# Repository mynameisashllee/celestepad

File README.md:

# celestepad
so... i play the game celeste a little bit, and thought it'd be cool to have a macropad with the bindings i use! (the defaults... haha)

check out the demo on [reddit!](https://www.reddit.com/r/celestegame/comments/1mbj6k7/i_made_a_mini_keypad_to_play_celeste/)

## features
- celestepad uses 7 keys (climb [z], dash [x], jump [c] and arrow keys. yes, they look inconveniently placed but they work pretty fine)
- regular ol case (enhanced with air dry clay and craft skills)

here's how it looks with just the circuit board and 3d print:

here's how the case looks alone:

## pcb
schematic:<br>

pcb (some strawberries because.. celeste): <br>

## bom
- 7x cherry MX switches
- 7x DSA keycaps
- 4x M3x5mx4mm heatset inserts
- 4x M3x16mm screws
- 1x XIAO RP2040
- 1x case (with 2 printed parts)
- some air dry clay, paint, hot glue and felt

## extras
this is my first time doing hardware! making a pcb! 3d modelling! had to google a lot but it was worth it (:
if i have time later on, i'll try and make a cute strawberry case that can open up to show the macropad. maybe with hinges? we'll see!

update: i ended up using air dry clay for fun and i'm really happy with the crafty look it's got!

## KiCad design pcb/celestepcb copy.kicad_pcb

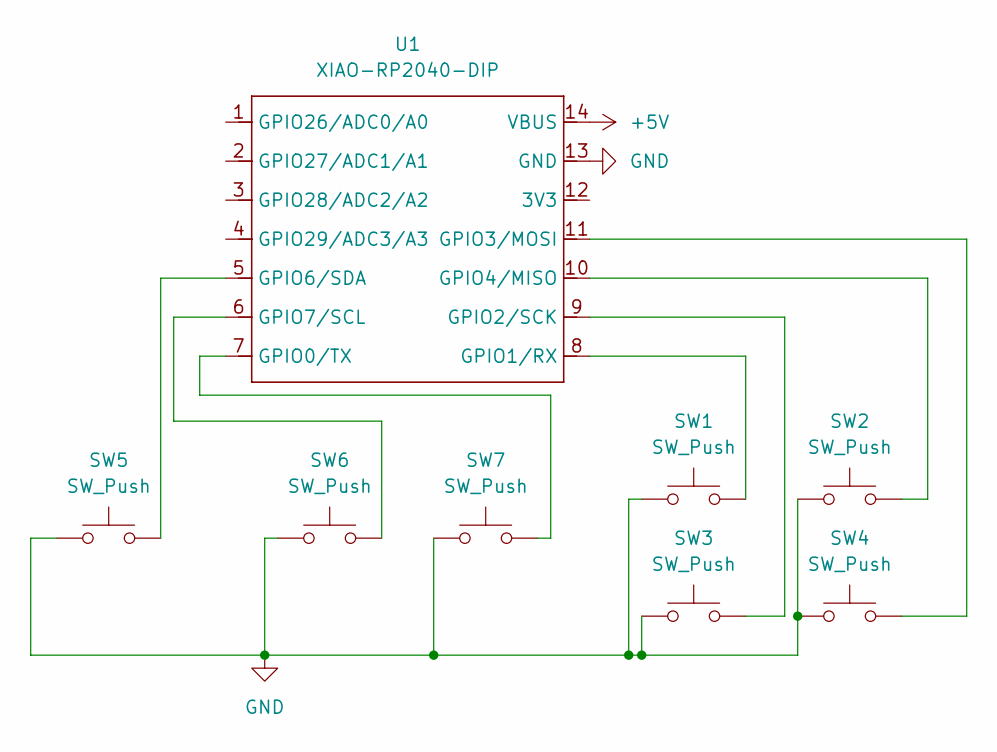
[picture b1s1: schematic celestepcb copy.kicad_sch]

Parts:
SW1, SW2, SW3, SW4, SW5, SW6, SW7: SW_Push; SW_Cherry_MX_1.00u_PCB
U1: XIAO-RP2040-DIP

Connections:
+5V: U1.14 (VBUS)
GND: SW1.1, SW2.1, SW3.1, SW4.1, SW5.1, SW6.1, SW7.1, U1.13 (GND)
unnamed: SW7.2, U1.7 (GPIO0/TX)
unnamed: SW1.2, U1.8 (GPIO1/RX)
unnamed: SW3.2, U1.9 (GPIO2/SCK)
unnamed: SW4.2, U1.11 (GPIO3/MOSI)
unnamed: SW2.2, U1.10 (GPIO4/MISO)
unnamed: SW5.2, U1.5 (GPIO6/SDA)
unnamed: SW6.2, U1.6 (GPIO7/SCL)

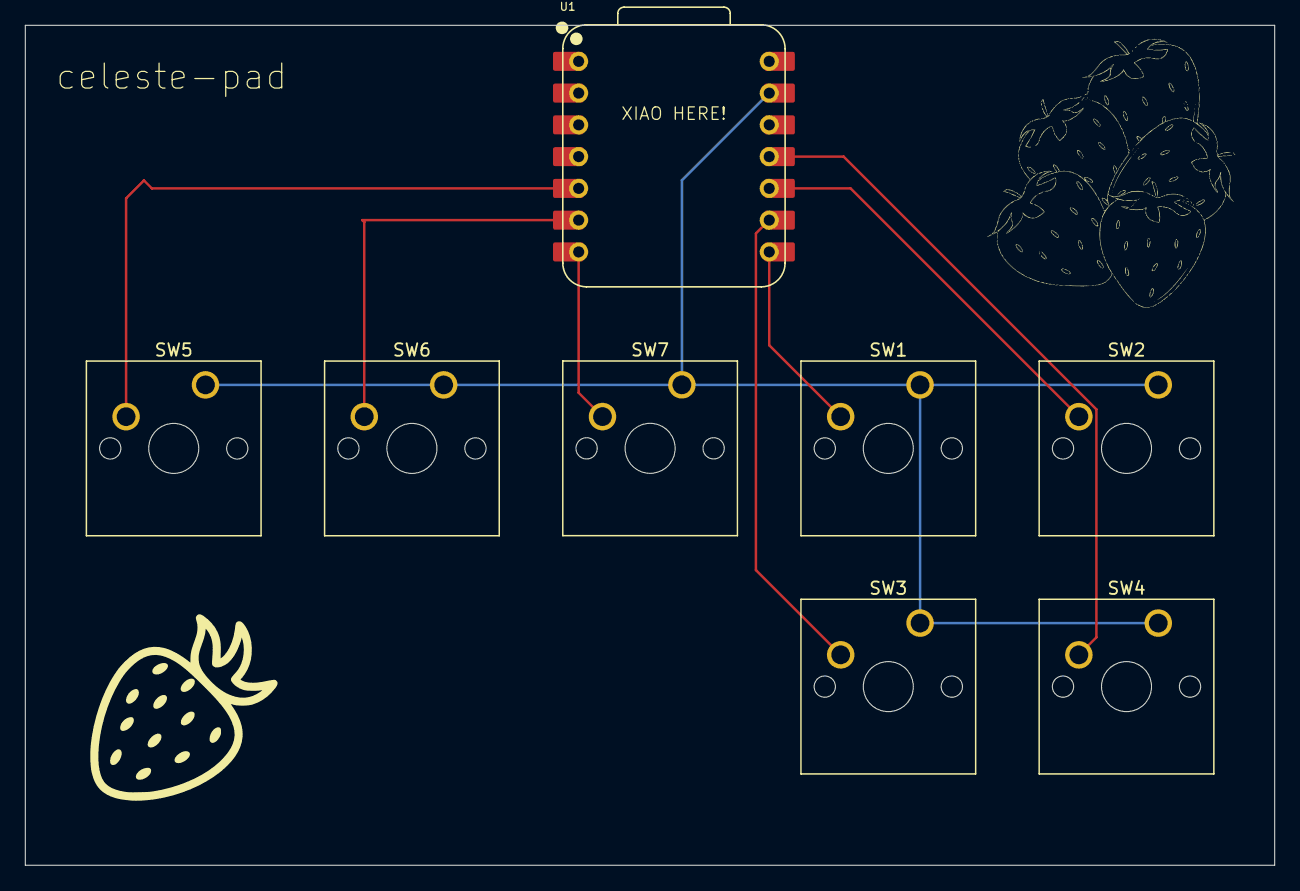
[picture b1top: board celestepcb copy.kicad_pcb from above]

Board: 2 copper layers, 99.9 x 67.2 mm, 8 parts (0 on the bottom side), 8 nets.

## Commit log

2025-05-18 upload imgs
2025-05-18 edits
2025-05-18 more edits
2025-07-28 post build updates
2025-08-14 add demo link
